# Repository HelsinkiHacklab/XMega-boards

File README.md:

XMega-boards
============

Breakouts for various XMegas with required supporting hardware

## Boards

  - XmegaA4U_v1: XMEGA A4U, TSSOP-8 regulator (TO-92 as an option), mini USB, 30 i/o pins.
    The first test board, works fine but the regulator used
    is no longer stocked by digikey/mouser. You can still use a TO-92 
    regulator though.
  - XmegaA4U_v2.0: XMEGA A4U, SOT-89 regulator, mini USB, 30 i/o pins.
    A slightly revised edition of v1. USB resistors removed, one LED added and regulator changed.
  - XmegaA4U_v2.1: XMEGA A4U, TSSOP-8 regulator, micro USB, 20 i/o pins.
    A smaller version with fewer pins and a split ground plane. Supports minimal 
    AVCC and AREF filtering. USB connector changed, reset button and 
    separate power connector removed.
  - XmegaA4U_v2.3: XMEGA A4U, SOT-89 regulator, micro USB, 30 i/o pins.
    Version with micro USB, some additional vcc/gnd pins and possibility to 
    add leds to pins E2 and E3.

## Software

For example Arduino IDE (well, XMegaduino) pin definitions for these boards (or at least some of them).

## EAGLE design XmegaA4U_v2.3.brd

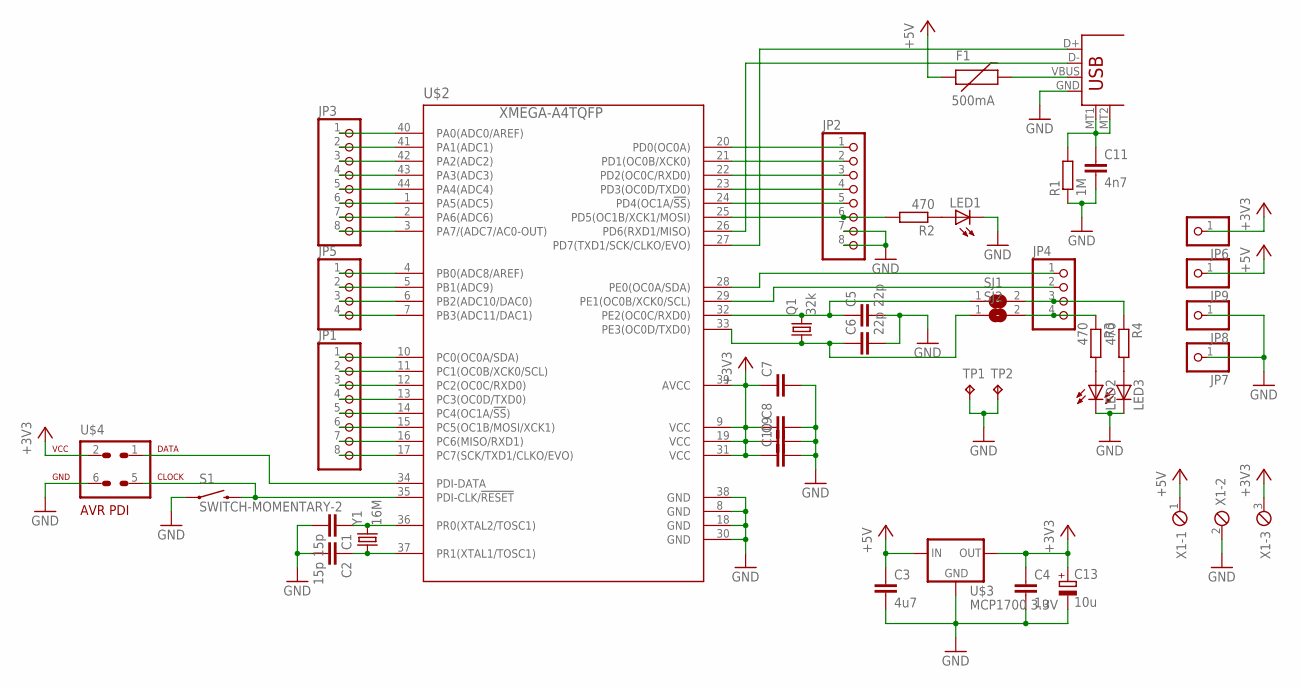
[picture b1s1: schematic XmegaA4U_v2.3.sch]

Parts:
C1, C2: 15p; C0603
C3: 4u7; C0805
C4: 1u; C0603
C5, C6: 22p; C0603
C7, C8, C9, C10: C-EUC0603; C0603
C11: 4n7; C0603
C13: 10u; SMC_A
F1: 500mA; 0805
JP1, JP2, JP3: PINHD_FIXEDPAD_ROUND-1X8; 1X08_ROUND
JP4, JP5: PINHD_FIXEDPAD_ROUND-1X4; 1X04_ROUND
JP6, JP7, JP8, JP9: PINHD_FIXEDPAD_ROUND-1X1; 1X01_ROUND
LED1, LED2, LED3: LEDCHIP-LED0603; CHIP-LED0603
Q1: 32k; TC26V_1.27
R1: 1M; R0603
R2, R3, R4: 470; R0603
S1: SWITCH-MOMENTARY-2; TACTILE_SWITCH_TALL
SJ1, SJ2: SJ_SMALL; SJ_2S-NO
TP1, TP2: TPTP15R; TP15R
U$2: XMEGA-A4TQFP; TQFP44
U$3: MCP1700 3.3V; SOT89-W
U$4: AVR-PDIVERT; AVR-ISP-6
U$5: USB+SHIELDMICRO; USB-MICROB
X1: MPT3; 3POL254
Y1: 16M; CRYSTAL-SMD-5X3

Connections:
+3V3: C4.1, C7.1, C8.1, C9.1, C10.1, C13.+, JP6.1, U$2.9 (VCC), U$2.19 (VCC), U$2.31 (VCC), U$2.39 (AVCC), U$3.3 (OUT), U$4.2, X1.3
+5V: C3.1, F1.1, JP9.1, U$3.2 (IN), U$3.TAB (IN), X1.1
GND: C1.2, C2.2, C3.2, C4.2, C5.2, C6.2, C7.2, C8.2, C9.2, C10.2, C11.2, C13.-, JP2.7, JP2.8, JP7.1, JP8.1, LED1.C, LED2.C, LED3.C, R1.1, S1.A2 (1), TP1.TP, TP2.TP, U$2.8 (GND), U$2.18 (GND), U$2.30 (GND), U$2.38 (GND), U$3.1 (GND), U$4.6, U$5.GND, X1.2
MTN: C11.1, R1.2, U$5.MT1, U$5.MT2
unnamed: C1.1, U$2.36 (PR0(XTAL2/TOSC1)), Y1.3 (2)
unnamed: C2.1, U$2.37 (PR1(XTAL1/TOSC1)), Y1.1
unnamed: F1.2, U$5.VBUS
unnamed: LED1.A, R2.1
unnamed: JP2.2, U$2.21 (PD1(OC0B/XCK0))
unnamed: JP2.3, U$2.22 (PD2(OC0C/RXD0))
unnamed: JP2.4, U$2.23 (PD3(OC0D/TXD0))
unnamed: JP2.5, U$2.24 (PD4(OC1A/!SS!))
unnamed: LED2.A, R3.2
unnamed: U$2.26 (PD6(RXD1/MISO)), U$5.D-
unnamed: LED3.A, R4.2
unnamed: JP3.2, U$2.41 (PA1(ADC1))
unnamed: JP3.3, U$2.42 (PA2(ADC2))
unnamed: JP3.4, U$2.43 (PA3(ADC3))
unnamed: JP3.5, U$2.44 (PA4(ADC4))
unnamed: JP3.6, U$2.1 (PA5(ADC5))
unnamed: JP3.7, U$2.2 (PA6(ADC6))
unnamed: JP1.2, U$2.11 (PC1(OC0B/XCK0/SCL))
unnamed: JP1.3, U$2.12 (PC2(OC0C/RXD0))
unnamed: JP1.4, U$2.13 (PC3(OC0D/TXD0))
unnamed: JP1.5, U$2.14 (PC4(OC1A/!SS!))
unnamed: JP1.6, U$2.15 (PC5(OC1B/MOSI/XCK1))
unnamed: JP1.7, U$2.16 (PC6(MISO/RXD1))
unnamed: JP5.2, U$2.5 (PB1(ADC9))
unnamed: JP5.3, U$2.6 (PB2(ADC10/DAC0))
unnamed: S1.B2 (2), U$2.35 (PDI-CLK/!RESET), U$4.5
unnamed: U$2.27 (PD7(TXD1/SCK/CLKO/EVO)), U$5.D+
unnamed: U$2.34 (PDI-DATA), U$4.1
XA0: JP3.1, U$2.40 (PA0(ADC0/AREF))
XA7: JP3.8, U$2.3 (PA7/(ADC7/AC0-OUT))
XB0: JP5.1, U$2.4 (PB0(ADC8/AREF))
XB3: JP5.4, U$2.7 (PB3(ADC11/DAC1))
XC0: JP1.1, U$2.10 (PC0(OC0A/SDA))
XC7: JP1.8, U$2.17 (PC7(SCK/TXD1/CLKO/EVO))
XD0: JP2.1, U$2.20 (PD0(OC0A))
XD5: JP2.6, R2.2, U$2.25 (PD5(OC1B/XCK1/MOSI))
XE0: JP4.1, U$2.28 (PE0(OC0A/SDA))
XE1: JP4.2, U$2.29 (PE1(OC0B/XCK0/SCL))
XE2: C5.1, Q1.2, SJ1.1, U$2.32 (PE2(OC0C/RXD0))
XE2S: JP4.3, R4.1, SJ1.2
XE3: C6.1, Q1.1, SJ2.1, U$2.33 (PE3(OC0D/TXD0))
XE3S: JP4.4, R3.1, SJ2.2

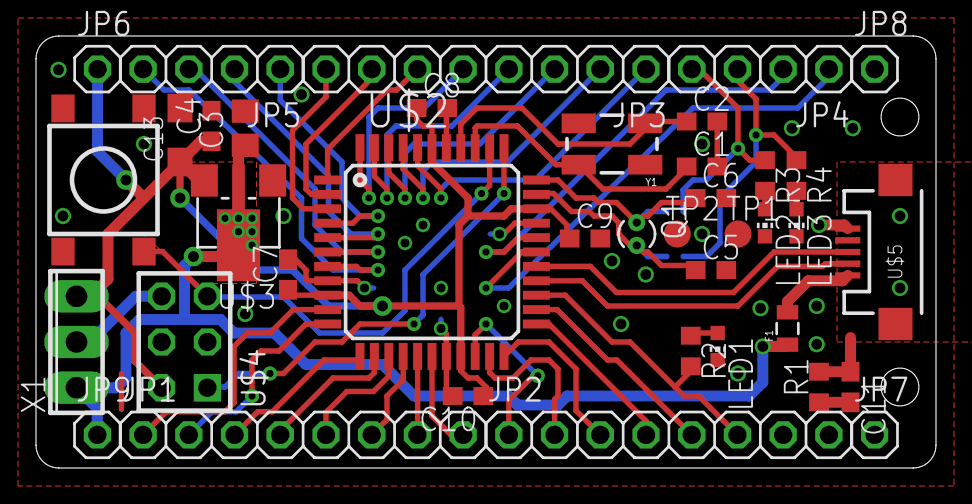
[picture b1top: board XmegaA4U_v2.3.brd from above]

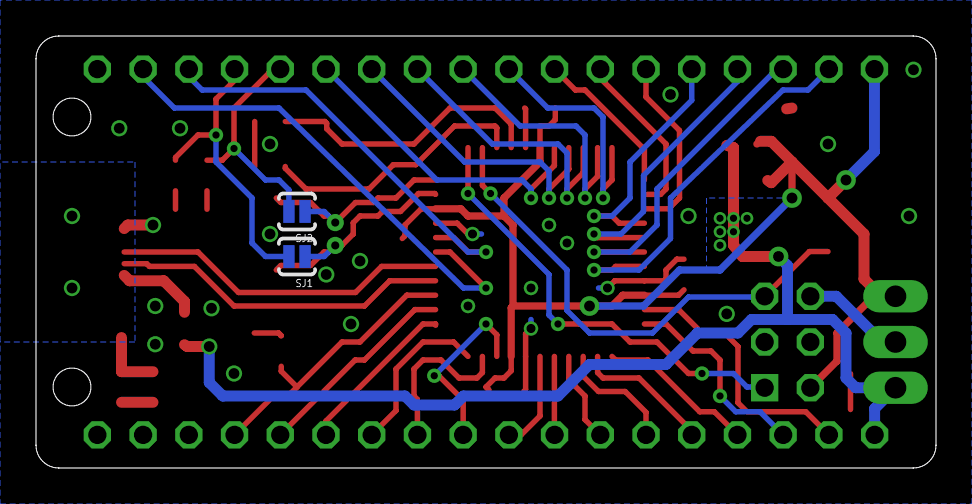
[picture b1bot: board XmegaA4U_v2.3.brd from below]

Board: 2 copper layers, 50.0 x 24.0 mm, 41 parts (2 on the bottom side), 46 nets.

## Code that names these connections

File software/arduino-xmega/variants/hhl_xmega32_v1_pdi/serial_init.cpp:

/*
  serial_init.cpp - Initialize serial ports for Arduino
  Part of Arduino - http://www.arduino.cc/

  Copyright (c) 2011 Karl Backstroem

  This library is free software; you can redistribute it and/or
  modify it under the terms of the GNU Lesser General Public
  License as published by the Free Software Foundation; either
  version 2.1 of the License, or (at your option) any later version.

  This library is distributed in the hope that it will be useful,
  but WITHOUT ANY WARRANTY; without even the implied warranty of
  MERCHANTABILITY or FITNESS FOR A PARTICULAR PURPOSE.  See the GNU
  Lesser General Public License for more details.

  You should have received a copy of the GNU Lesser General
  Public License along with this library; if not, write to the
  Free Software Foundation, Inc., 59 Temple Place, Suite 330,
  Boston, MA  02111-1307  USA

*/

// Preinstantiate Objects //////////////////////////////////////////////////////

#define SERIAL_DEFINE(name, usart_port, port_nr) \
ring_buffer name##rx_buffer = { { 0 }, 0, 0 }; \
ISR(USART##usart_port##port_nr##_RXC_vect) \
{ \
  unsigned char c = USART##usart_port##port_nr.DATA; \
  store_char(c, &name##rx_buffer); \
} \
HardwareSerial name (&name##rx_buffer, &USART##usart_port##port_nr, &PORT##usart_port, (port_nr ? PIN6_bm : PIN2_bm), (port_nr ? PIN7_bm : PIN3_bm));

// The comments are reminders on where these USARTs actually are (and pin numbers as on the rev1 board)
SERIAL_DEFINE(Serial, C, 0); // -> PC1/PC3 == 17/19
SERIAL_DEFINE(Serial1, C, 1); // -> PC6/PC7 == 22/23
SERIAL_DEFINE(Serial2, D, 0); // -> PD2/PD3 == 26/27
/* SERIAL_DEFINE(Serial3, D, 1);  This is USB */
SERIAL_DEFINE(Serial3, E, 0); // -> PE2/PE3 == 2/3

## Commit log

2012-10-31 the files and BOM list exactly as I got them from Heikki, so comments in finnish etc
2012-11-04 Link to an image of the board
2012-11-13 renamed to immediately indicate correct chip
2012-11-13 high-rez photo of the board for soldering reference with schematic and bom (notes in finnish, sorry about that)
2012-11-13 the pic is added
2013-01-28 Added version 2 of the A4U breakout (created Nov 2012)
2013-01-28 Added version 2.1 of the A4U breakout (a bit smaller, fewer pins broken out, created Nov 2012)
2013-01-28 Renamed the original A4U breakout files, removed some unnecessary silkscreen texts
2013-01-28 Readme updated.
2013-02-02 rename these to correspond to revision
2013-02-03 todos
2013-02-03 patching xmegaduino
2013-02-03 mappings
2013-02-03 typo fix, moar mappings
2013-02-03 started writing pin mappings
2013-02-03 typo fixes in mappings
2013-02-03 pin mappings
2013-02-03 instructions
2013-02-03 the old mappings should not have been touched
2013-02-03 pin numbers start from 0
2013-02-03 see previous
2013-02-03 this probably is the correct way to map channel with the value returned from digital_pin_to_timer_PGM
2013-02-03 we use "RTC" even though the external rtc xtal is not there
2013-02-03 updated readmes
2013-02-03 Update software/arduino-xmega/README.md
    URL for update instructions just in case it was needed.
2013-02-03 Revert "updated readmes"
    This reverts commit 211973fab126c7de75e43201224765fd6092a9ae.
2013-02-03 oops...
    Revert "Revert "updated readmes""
    This reverts commit ee428003964d35986cc8aaf2dc729479c3b1fa4f.
2013-02-03 made a note of this
2013-02-03 Added photos of the three latest boards
2013-02-03 Let's not include the memory size in the board names.
2013-02-03 The led option was already in 2.0
2013-02-14 First A3U photo
2013-02-25 Artistic version from the .brd file
2013-05-03 Version 2.3 added
2013-05-14 Basic standalone demos for xmega development
2013-05-14 Build scripts for windows + modified usbasp
    Needs patched avrdude and pdi capable usbasp firmware
    (http://szulat.blogspot.fi/2012/08/atxmega-programmer-for-050.html
    http://ketturi.kapsi.fi/2013/05/programming-xmega-with-usbasp-avrdude/)
2013-05-14 Typo fixes
2013-05-14 More small typo fixes
2013-06-28 note the pin numbers for the serial ports
2013-08-06 Added detailed instructions.

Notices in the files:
parts and their libraries:
SparkFun: Licensing: CC v3.0 Share-Alike You are welcome to use this library for commercial purposes.
